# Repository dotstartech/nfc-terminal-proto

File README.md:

# nfc-terminal-proto
NFC Terminal Prototype

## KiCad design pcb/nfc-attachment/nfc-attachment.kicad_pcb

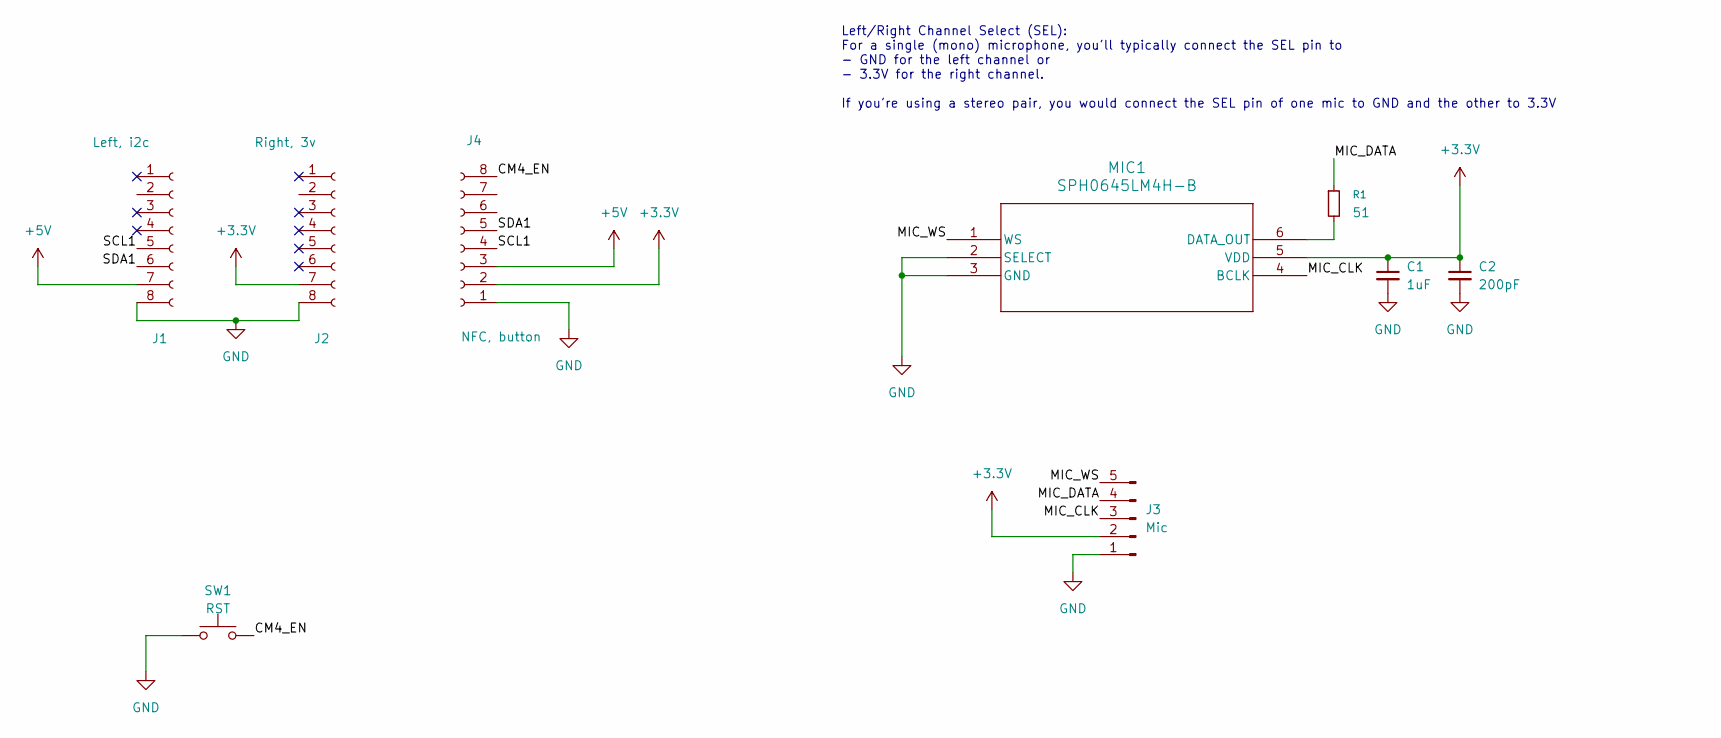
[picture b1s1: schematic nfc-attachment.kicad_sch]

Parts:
C1: 1uF; C_0603_1608Metric
C2: 200pF; C_0603_1608Metric
J1: Left, i2c; PinHeader_1x08_P2.54mm_Vertical
J2: Right, 3v; PinHeader_1x08_P2.54mm_Vertical
J3: Mic; PinHeader_1x05_P2.54mm_Vertical
J4: NFC, button; PinHeader_1x08_P2.54mm_Vertical
MIC1: SPH0645LM4H-B; SPH0645LM4H-B_KNO
R1: 51; R_0402_1005Metric
SW1: RST; SW_SPST_PTS810; LCSC C116501

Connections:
+3.3V: C1.1, C2.1, J2.7, J3.2, J4.2, MIC1.5 (VDD)
+5V: J1.7, J4.3
/CM4_EN: J4.8, SW1.2
/MIC_CLK: J3.3, MIC1.4 (BCLK)
/MIC_DATA: J3.4, R1.1
/MIC_WS: J3.5, MIC1.1 (WS)
/SCL1: J1.5, J4.4
/SDA1: J1.6, J4.5
GND: C1.2, C2.2, J1.8, J2.8, J3.1, J4.1, MIC1.2 (SELECT), MIC1.3 (GND), SW1.1
unnamed: MIC1.6 (DATA_OUT), R1.2

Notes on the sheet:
Left/Right Channel Select (SEL): For a single (mono) microphone, you'll typically connect the SEL pin to - GND for the left channel or - 3.3V for the right channel. If you're using a stereo pair, you would connect the SEL pin of one mic to GND and the other to 3.3V

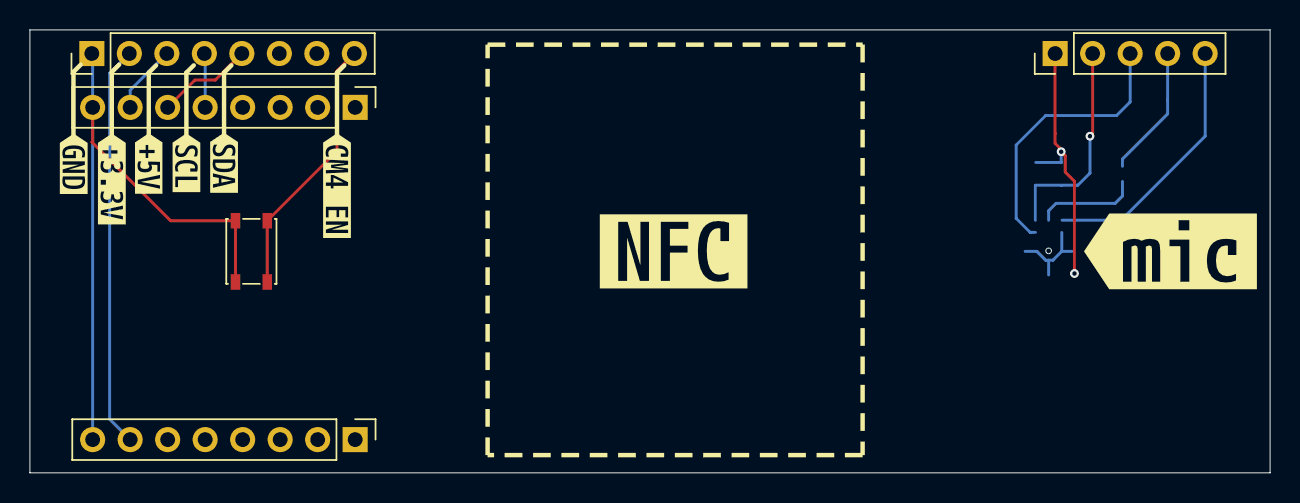
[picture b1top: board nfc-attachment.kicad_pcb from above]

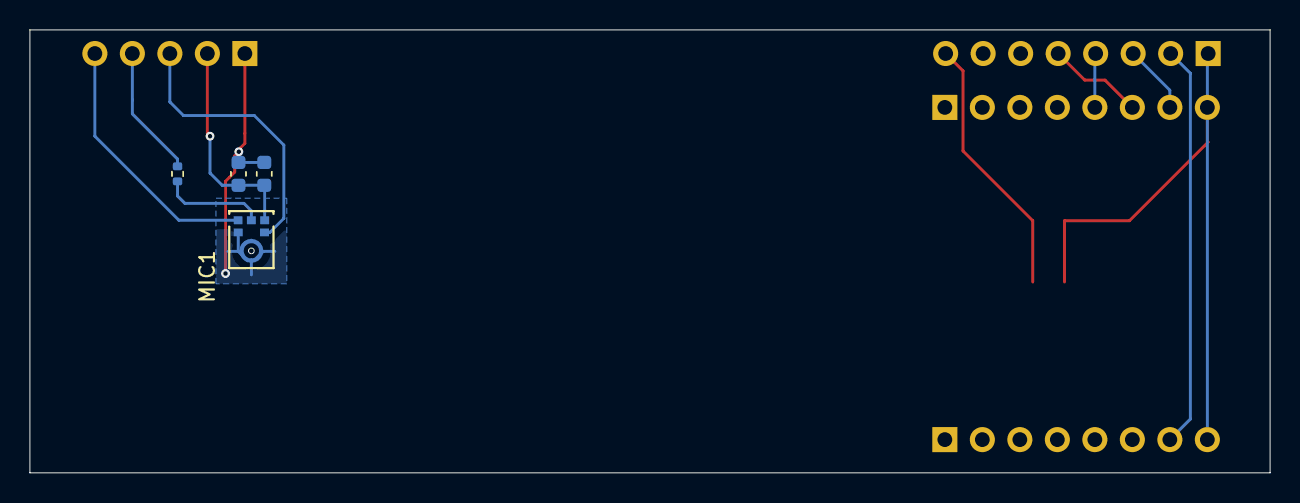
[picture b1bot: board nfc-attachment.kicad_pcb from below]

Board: 2 copper layers, 84.0 x 30.0 mm, 17 parts (4 on the bottom side), 10 nets.

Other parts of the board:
kibuzzard-68ADC165: G***; kibuzzard-68ADC165
kibuzzard-68ADC191: G***; kibuzzard-68ADC191
kibuzzard-68AEE2C2: G***; kibuzzard-68AEE2C2
kibuzzard-68AEE2D0: G***; kibuzzard-68AEE2D0
kibuzzard-68AEE2DF: G***; kibuzzard-68AEE2DF
kibuzzard-68AEE21F: G***; kibuzzard-68AEE21F
kibuzzard-68AEE211: G***; kibuzzard-68AEE211
kibuzzard-68AEE235: G***; kibuzzard-68AEE235

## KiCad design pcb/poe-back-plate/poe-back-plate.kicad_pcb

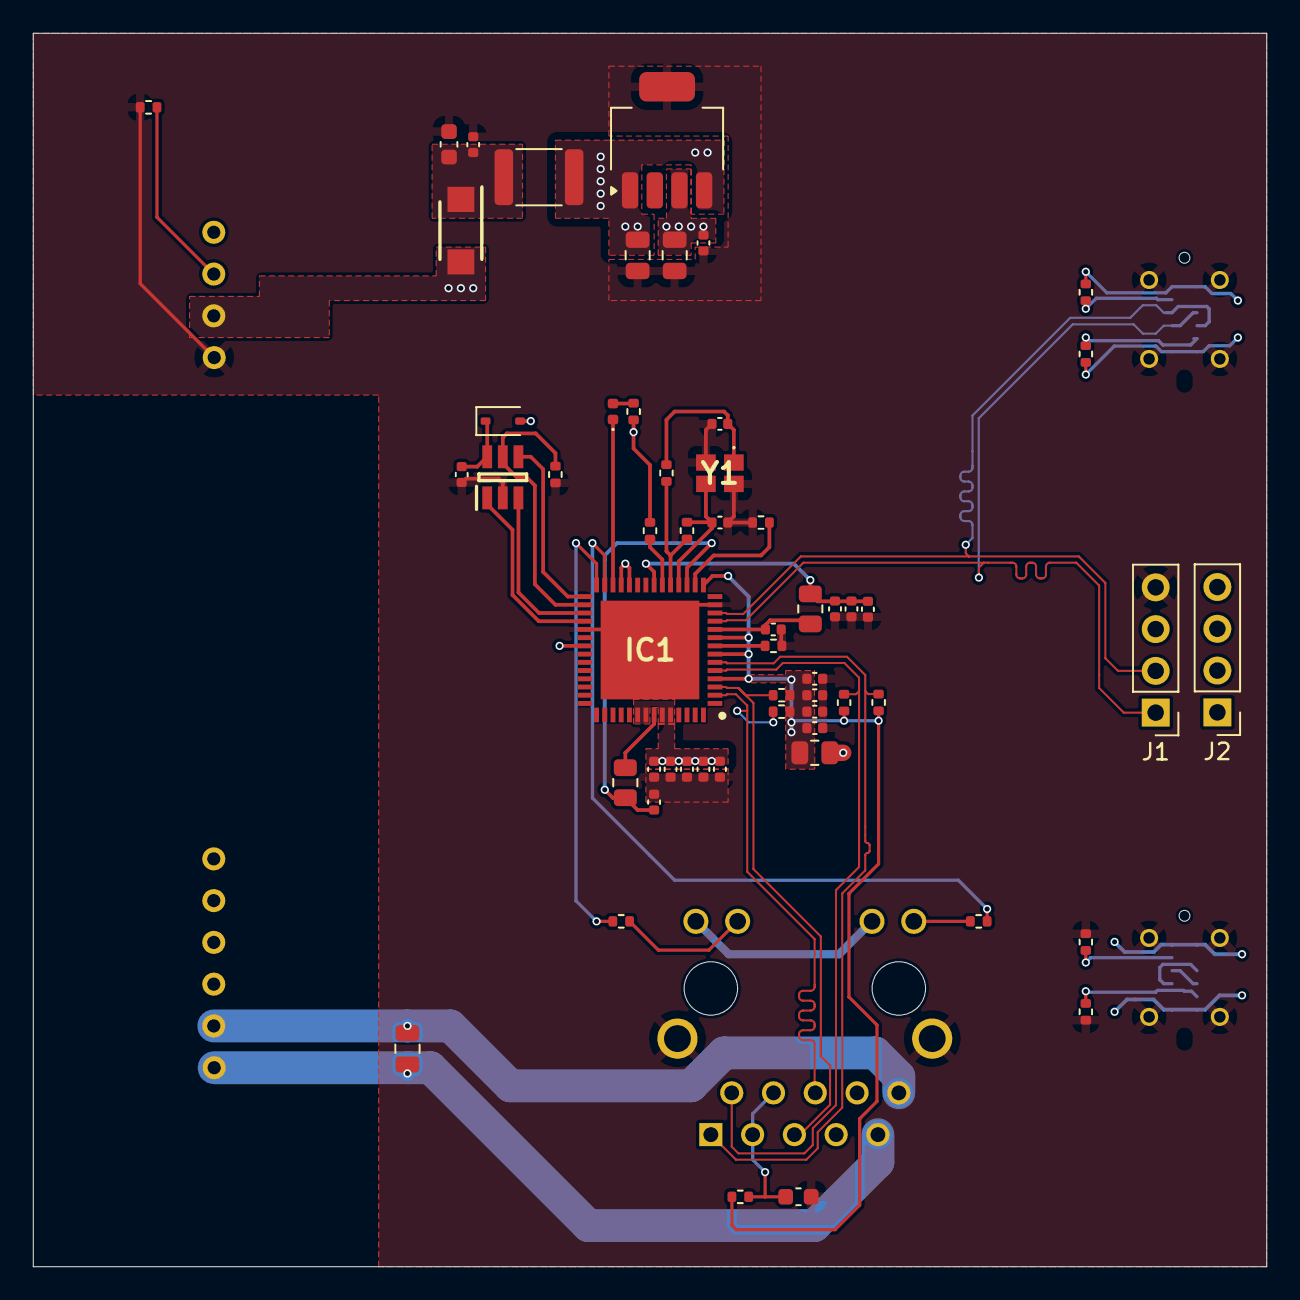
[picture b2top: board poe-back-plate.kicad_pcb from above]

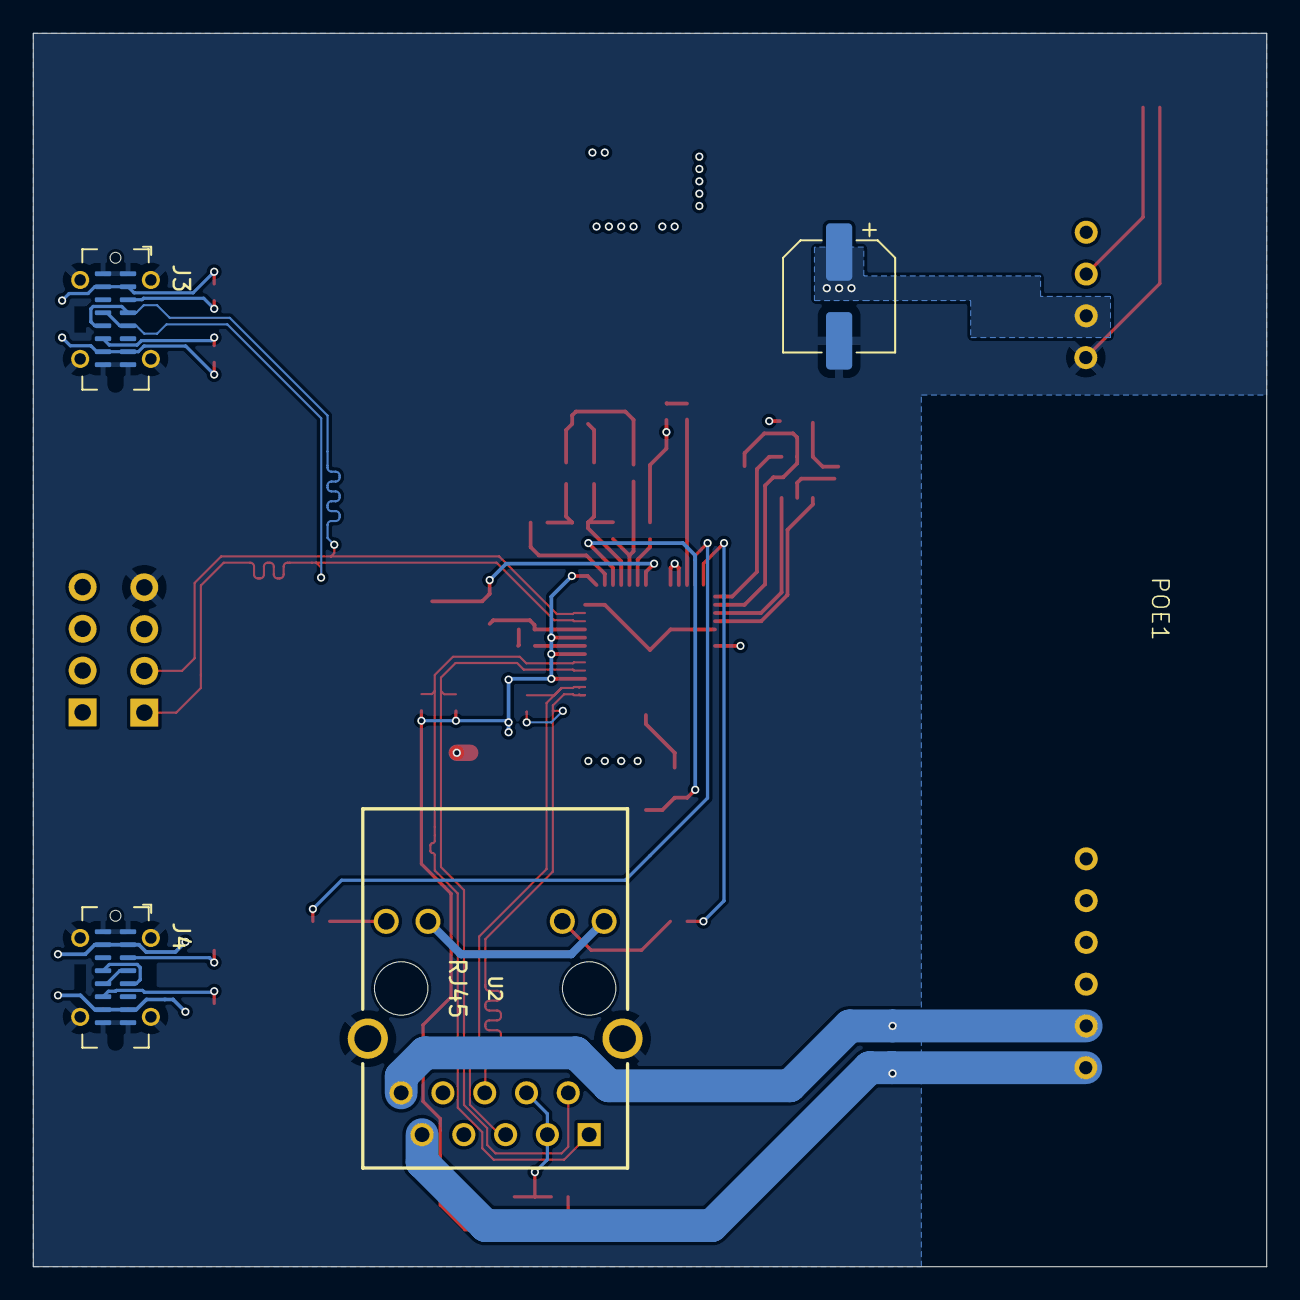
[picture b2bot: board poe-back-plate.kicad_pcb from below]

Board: 6 copper layers, 75.0 x 75.0 mm, 61 parts (5 on the bottom side), 42 nets.

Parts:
C1, C2, C3, C4, C5, C6, C7, C8, C9, C11, C12, C13, C14, C16, C20, C22: 100nF; C_0402_1005Metric
C10: 1uF; C_0402_1005Metric
C15, C18: 24pF; C_0402_1005Metric
C17, C19: 1uF; C_0805_2012Metric
C21: 1uF; C_0603_1608Metric
C23: 22nF; C_0603_1608Metric
C24: 10nF; C_0805_2012Metric
C25: 470µF; CP_Elec_6.3x7.7
D1: GREEN; LED_0402_1005Metric
D2: B0540WS; D_SOD-323
D3: SS54F; SODFL4626X120N
FB1, FB2, FB3: BLM21PG221SN1D; R_0805_2012Metric
FB4: CBM453215U101T; R_1812_4532Metric
IC1: LAN9500A-ABZJ; QFN50P800X800X100-57N-D
IC2: 93LC66AT-I_OT; SOT95P270X145-6N
J1: USB + Power; PinHeader_1x04_P2.54mm_Vertical
J2: UART + I2C; PinHeader_1x04_P2.54mm_Vertical
J3, J4: USB_C_Receptacle_USB2.0_14P; USB_C_Receptacle_G-Switch_GT-USB-7051x
POE1: AG5405
R1, R2: 12K; R_0402_1005Metric
R3, R5: 0; R_0402_1005Metric
R4: 1M; R_0402_1005Metric
R6, R12, R13: 3.3K; R_0402_1005Metric
R7: 10K; R_0402_1005Metric
R8, R10: 56K; R_0402_1005Metric
R9, R11: 5.1K; R_0402_1005Metric
R14: 10; R_0402_1005Metric
R15, R16, R17, R18: 49.9; R_0402_1005Metric
R19: 50K; R_0402_1005Metric
U1: LP38693MP-3.3; SOT-223-5
U2: HY931147C
Y1: ECS-250-18-36B2-CTY-TR; ECS2501836B2CTYTR

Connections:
+3.3V: C1.2, C2.2, C4.2, C6.2, C8.2, C19.2, C20.2, D2.2 (A), FB1.1, IC1.24 (NRESET), IC1.25 (VDD33IO_1), IC1.35 (VDD33IO_2), IC1.48 (VDD33IO_3), IC1.49 (TEST1), IC1.51 (VDD33IO_4), IC1.52 (VDD33IO_5), R3.1, R6.2, U1.3 (OUT), U2.P$11 (Y+), U2.P$13 (G+)
+5V: C17.2, FB4.2, J1.3, J3.A4 (VBUS), J3.A9 (VBUS), J3.B4 (VBUS), J3.B9 (VBUS), J4.A4 (VBUS), J4.A9 (VBUS), J4.B4 (VBUS), J4.B9 (VBUS), R8.2, R10.2, U1.1 (EN), U1.4 (IN)
/PoE/ETH1_LEDG: IC1.27 (NLNKA_LED/GPIO9), R12.2
/PoE/ETH1_LEDY: IC1.28 (NSPD_LED/GPIO10), R13.2
/PoE/POE_5V: C21.1, C22.1, D3.1 (K), FB4.1
/PoE/RXN: IC1.5 (RXN), R15.2, U2.P$2 (RX-)
/PoE/RXP: IC1.6 (RXP), R16.2, U2.P$1 (RX+)
/PoE/TXN: IC1.2 (TXN), R17.2, U2.P$6 (TX-)
/PoE/TXP: IC1.3 (TXP), R18.2, U2.P$5 (TX+)
/PoE/VDD33A: C3.2, C5.2, C7.2, C9.2, FB1.2, IC1.4 (VDD33A_1), IC1.7 (NC_1), IC1.9 (VDD33A_2), IC1.15 (VDD33A_3), R14.1, R15.1, R16.1, R17.1, R18.1
/USB to Ethernet/CRYSTAL_XI: C18.2, IC1.18 (XI), R4.2, Y1.3 (OUT/IN)
/USB to Ethernet/CRYSTAL_XO: IC1.19 (XO), R4.1, R5.1
/USB to Ethernet/EECLK_GPIO3: IC1.29 (EECLK/PWR_SEL), IC2.4 (CLK)
/USB to Ethernet/EECS_GPIO0: IC1.30 (EECS), IC2.5 (CS), R7.1
/USB to Ethernet/EEDI_GPIO1: IC1.32 (EEDI), IC2.1 (DO)
/USB to Ethernet/EEDO_GPIO2: IC1.31 (EEDO/AUTOMDIX_EN), IC2.3 (DI)
/USB to Ethernet/ETH1_LED_FDX: D1.1 (K), IC1.26 (NFDX_LED/GPIO8)
/USB to Ethernet/USBDN: IC1.11 (USBDM), J1.1, J3.A7 (D-), J3.B7 (D-)
/USB to Ethernet/USBDP: IC1.12 (USBDP), J1.2, J3.A6 (D+), J3.B6 (D+)
/USB to Ethernet/VDDCORE: C10.2, C11.2, C12.2, FB2.1, FB3.1, IC1.21 (VDDCORE_1), IC1.50 (VDDCORE_2)
/USB to Ethernet/VDDPLL: C14.2, FB3.2, IC1.10 (VDDPLL)
/USB to Ethernet/VDDUSBPLL: C13.2, FB2.2, IC1.17 (VDDUSBPLL)
GND: C1.1, C2.1, C3.1, C4.1, C5.1, C6.1, C7.1, C8.1, C9.1, C10.1, C11.1, C12.1, C13.1, C14.1, C15.1, C16.1, C17.1, C18.1, C19.1, C20.1, C21.2, C22.2, C23.2, C25.2, IC1.13 (TEST2), IC1.33 (TEST3), IC1.57 (VSS), IC2.2 (VSS), J1.4, J3.A1 (GND), J3.A12 (GND), J3.B1 (GND), J3.B12 (GND), J3.S1 (SHIELD), J4.A1 (GND), J4.A12 (GND), J4.B1 (GND), J4.B12 (GND), J4.S1 (SHIELD), POE1.7 (-VDC), R1.1, R2.1, R7.2, R9.2, R11.2, R19.2, U1.5 (GND), U2.GND1, U2.GND2, Y1.2 (GND_1), Y1.4 (GND_2)
unnamed: D1.2 (A), R6.1
unnamed: C16.2, D2.1 (K), IC2.6 (VCC)
unnamed: C25.1, D3.2 (A), POE1.8 (+VDC_)
unnamed: IC1.8 (EXRES), R1.2
unnamed: IC1.16 (USBRBIAS), R2.2
unnamed: IC1.20 (VBUS_DET), R3.2
unnamed: J3.A5 (CC1), R8.1
unnamed: J3.B5 (CC2), R10.1
unnamed: J4.A5 (CC1), R9.1
unnamed: J4.B5 (CC2), R11.1
unnamed: J4.A6 (D+), J4.B6 (D+)
unnamed: J4.A7 (D-), J4.B7 (D-)
unnamed: POE1.9 (ADJ), R19.1
unnamed: C24.1, POE1.1 (VIN+), U2.P$9 (V+)
unnamed: C24.2, POE1.2 (VIN-), U2.P$10 (V-)
unnamed: R12.1, U2.P$14 (G-)
unnamed: C23.1, R14.2, U2.P$3 (RXCT), U2.P$4 (TXCT)
unnamed: R13.1, U2.P$12 (Y-)
unnamed: C15.2, R5.2, Y1.1 (IN/OUT)

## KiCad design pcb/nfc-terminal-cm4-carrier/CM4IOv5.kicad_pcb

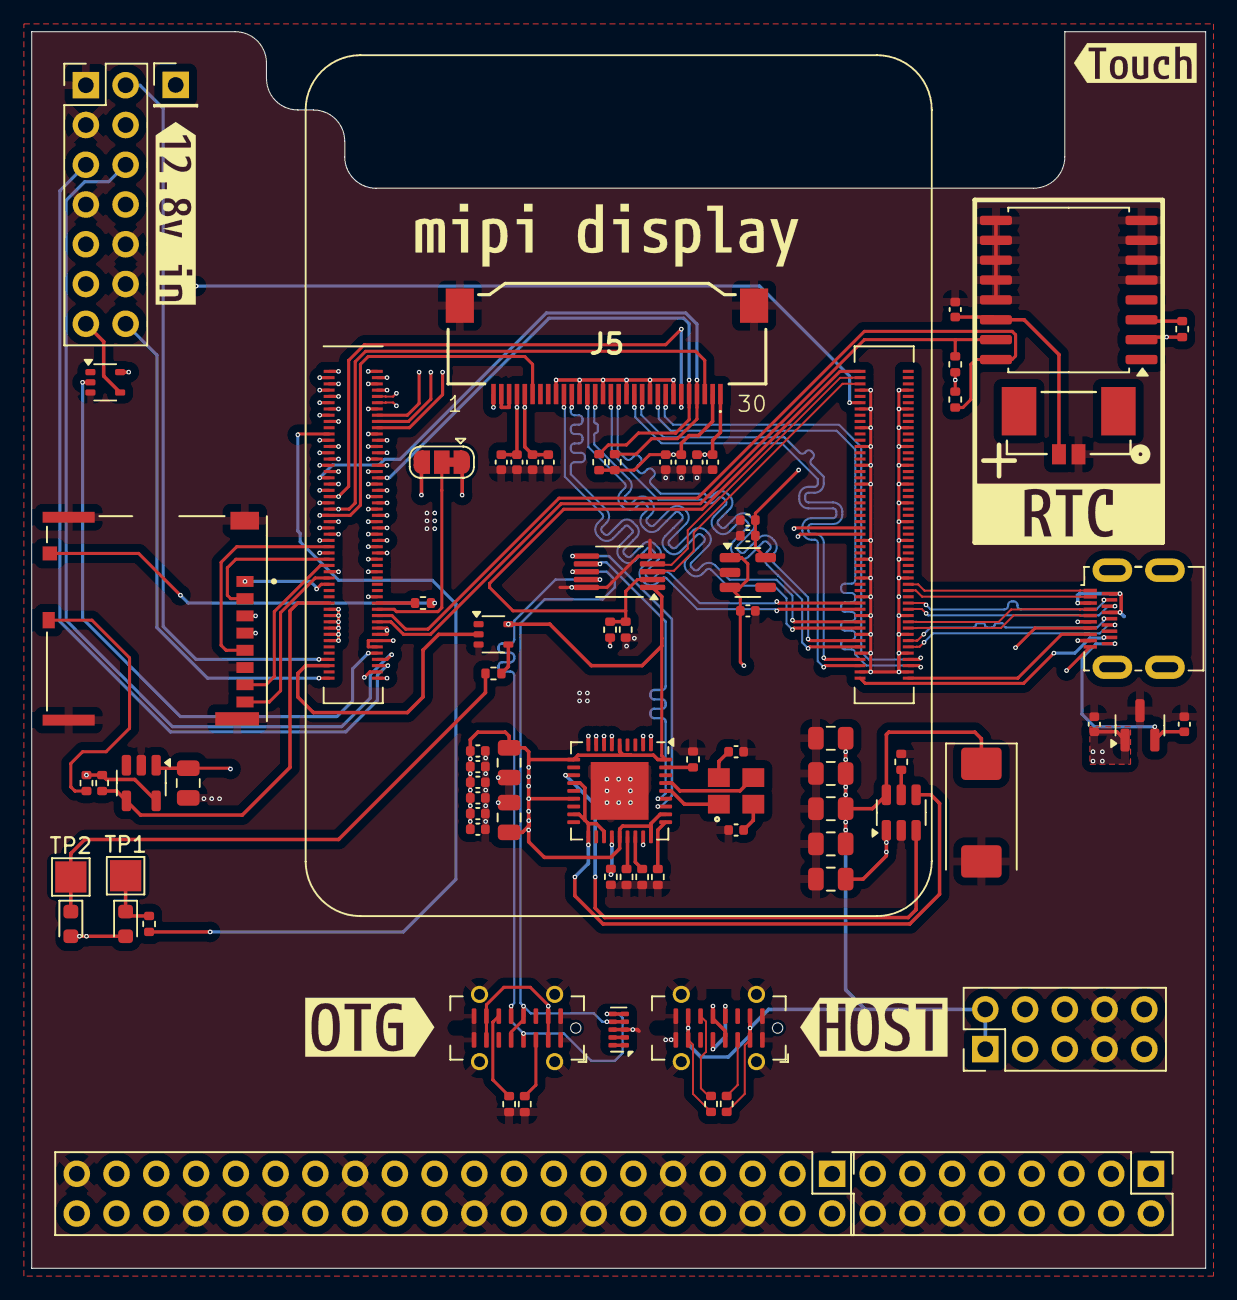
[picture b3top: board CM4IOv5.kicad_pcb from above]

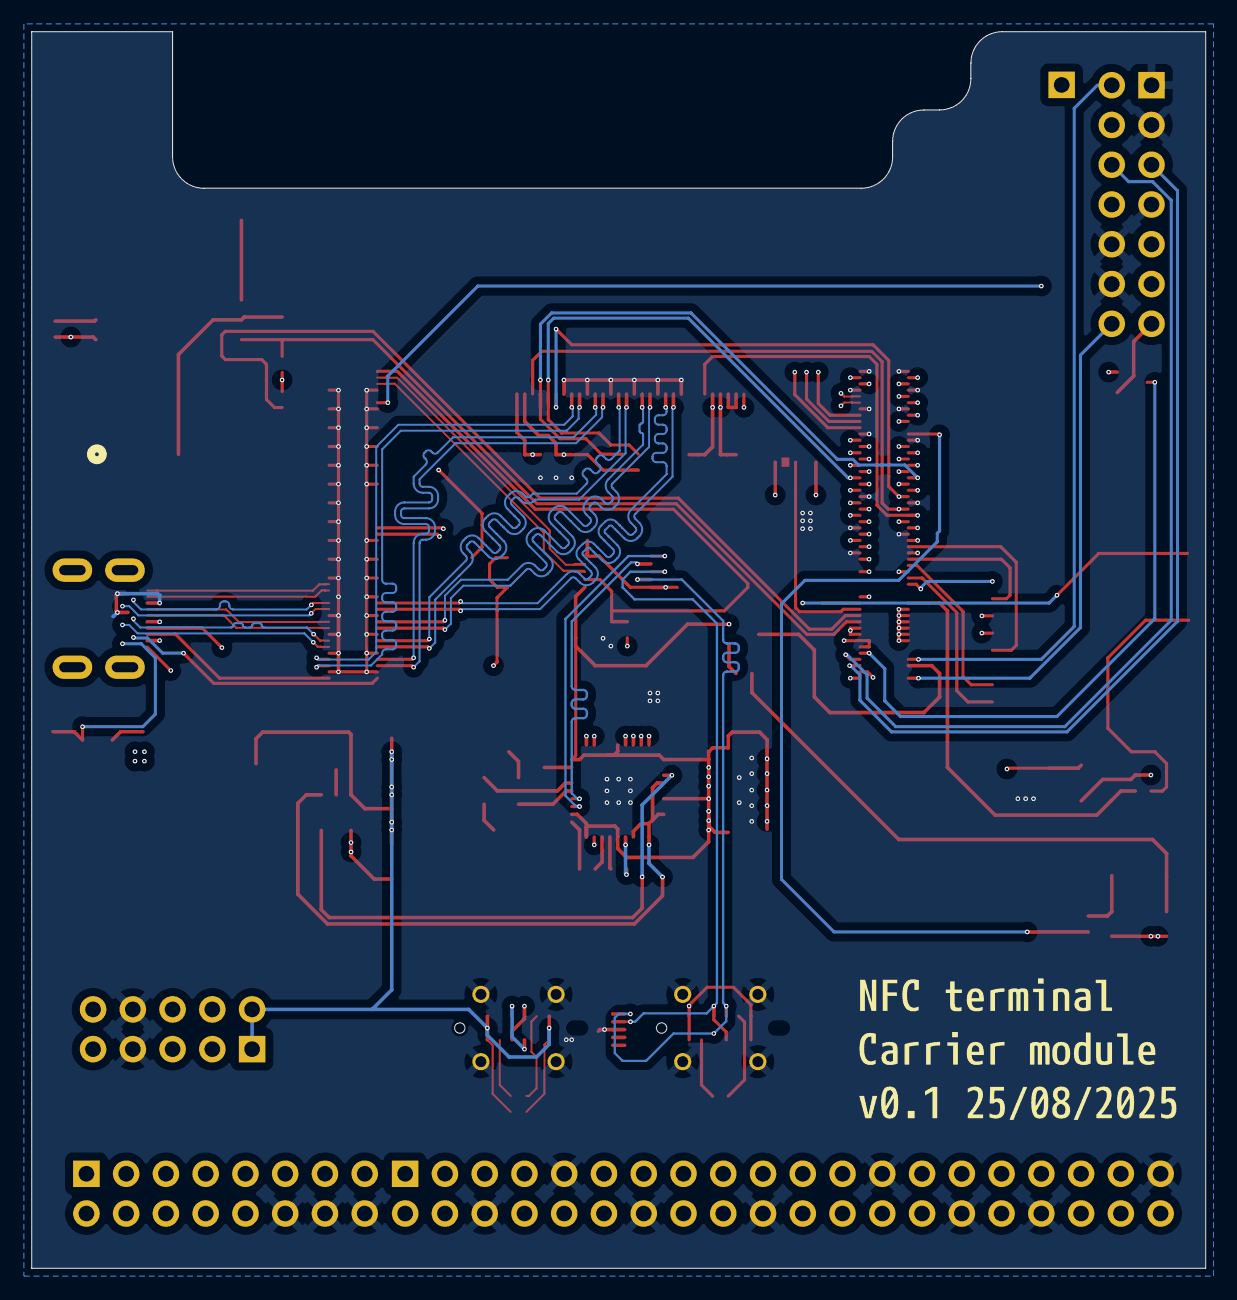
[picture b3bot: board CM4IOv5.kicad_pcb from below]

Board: 6 copper layers, 75.0 x 79.0 mm, 89 parts (2 on the bottom side), 132 nets.

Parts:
C1, C2: 27pF; C_0402_1005Metric
C3, C4, C11, C13, C14, C15, C16, C31: 10u; C_0805_2012Metric
C5, C6, C7, C8, C9, C10, C17, C18, C19, C22, C23, C24, C27, C28: 100n; C_0402_1005Metric
C12: 100uF; CP_EIA-7343-31_Kemet-D
C20, C21: 10uF; C_0402_1005Metric
C25, C26, C29, C30: 1uF; C_0402_1005Metric
D1: LED Green; LED_0603_1608Metric
D2: LED Red; LED_0603_1608Metric
J1, J2: USB_C_Receptacle_USB2.0_14P; USB_C_Receptacle_G-Switch_GT-USB-7051x
J3: Conn_02x05_Odd_Even; PinHeader_2x05_P2.54mm_Vertical
J4: Conn_01x02_Socket; CONN02_533984002_MOL
J5: F31L-1A7H1-11030; F31L1A7H111030
J6: 690-019-298-412; HDMI_Micro-D_Molex_46765-1x01
J7: Conn_02x07_Odd_Even; PinHeader_2x07_P2.54mm_Vertical
J10: THD-20-R; PinHeader_2x20_P2.54mm_Vertical
J15: THD-20-R; PinHeader_2x08_P2.54mm_Vertical
J16: Micro_SD_Card_Det; SDCARD_MOLEX_503398-1892
J17: UART; PinHeader_1x01_P2.54mm_Vertical
JP1: GPIO reference; SolderJumper-3_P1.3mm_Bridged12_RoundedPad1.0x1.5mm
Module1: ComputeModule4; Raspberry-Pi-4-Compute-Module
R1, R2, R14, R15: 2.2K 1%; R_0402_1005Metric
R3, R4, R5, R7: 36K 1%; R_0402_1005Metric
R6, R22: 12K 1%; R_0402_1005Metric
R8, R9: 5.1k; R_0402_1005Metric
R10, R12: 56K; R_0402_1005Metric
R11: 15K 1%; R_0402_1005Metric
R13: 10K; R_0402_1005Metric
R16, R19: 1k; R_0402_1005Metric
R20, R21: nf; R_0402_1005Metric
R23, R24: 4.7k; R_0402_1005Metric
TP1, TP2: TestPoint; TestPoint_Pad_2.0x2.0mm
U1: FSUSB42MUX; MSOP-10_3x3mm_P0.5mm
U2: USB2514B-I/M2; QFN-36-1EP_6x6mm_P0.5mm_EP3.7x3.7mm
U3: TPD4EUSB30; USON-10_2.5x1.0mm_P0.5mm
U4: AP22653W6; SOT-23-6
U5: DS3231M; SOIC-16W_7.5x10.3mm_P1.27mm
U6: RT9742SNGV; SOT-23
U7: LP5907MFX-2.8; SOT-23-5
U8, U9: 74LVC1G07SE-7; SOT-353_SC-70-5
U10: RT9742GGJ5; SOT-23-5
Y1: ABM8G-24.000MHZ-18-D2Y-T; ABM8G
kibuzzard-68AB3D2F: G***; kibuzzard-68AB3D2F
kibuzzard-68AB3EB0: G***; kibuzzard-68AB3EB0
kibuzzard-68AB3F8D: G***; kibuzzard-68AB3F8D
kibuzzard-68AB3F22: G***; kibuzzard-68AB3F22
kibuzzard-68AB3FA7: G***; kibuzzard-68AB3FA7
kibuzzard-68AB540C: G***; kibuzzard-68AB540C
kibuzzard-68AC31CB: G***; kibuzzard-68AC31CB
kibuzzard-68AC3314: G***; kibuzzard-68AC3314

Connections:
+2.8v: C21.2, C22.2, C24.1, C26.1, C28.1, C30.1, J5.4 (VCI_4), J5.5 (IOVCC_5), U7.5 (OUT)
/+3.3v: C3.1, C4.1, C5.1, C6.1, C7.1, C8.1, C9.1, C10.1, C20.2, C23.1, C25.1, C27.1, C29.1, D1.2 (A), D2.2 (A), J5.29 (TP_VCI_29), J5.30 (TP_IOVCC_30), J10.1, J10.17, J15.15, JP1.1 (A), Module1.84 (+3.3v_(Output)), Module1.86 (+3.3v_(Output)), R13.2, R14.1, R15.1, R20.1, R22.1, R23.1, R24.1, U1.1 (VCC), U2.5 (VDDA33), U2.10 (VDDA33), U2.15 (VDD33), U2.23 (VDD33), U2.27 (VBUS_DET), U2.29 (VDDA33), U2.36 (VDDA33), U5.2 (VCC), U7.1 (IN), U7.3 (EN), U9.5 (VCC), U10.5 (IN)
/+5v: C11.1, C18.1, J10.2, J10.4, J15.13, Module1.77 (+5v_(Input)), Module1.79 (+5v_(Input)), Module1.81 (+5v_(Input)), Module1.83 (+5v_(Input)), Module1.85 (+5v_(Input)), Module1.87 (+5v_(Input)), U4.1 (IN), U6.1 (IN), U8.5 (VCC)
/CM4_GPIO ( Ethernet, GPIO, SDCARD)/+1.8v: JP1.3 (B), Module1.88 (+1.8v_(Output)), Module1.90 (+1.8v_(Output))
/CM4_GPIO ( Ethernet, GPIO, SDCARD)/AIN0: J7.5, Module1.96 (AnalogIP0)
/CM4_GPIO ( Ethernet, GPIO, SDCARD)/AIN1: J7.6, Module1.94 (AnalogIP1)
/CM4_GPIO ( Ethernet, GPIO, SDCARD)/EEPROM_nWP: J7.4, Module1.20 (EEPROM_nWP)
/CM4_GPIO ( Ethernet, GPIO, SDCARD)/ETH_LEDG: J15.9, Module1.17 (Ethernet_nLED2(3.3v))
/CM4_GPIO ( Ethernet, GPIO, SDCARD)/ETH_LEDY: J15.10, Module1.15 (Ethernet_nLED3(3.3v))
/CM4_GPIO ( Ethernet, GPIO, SDCARD)/GLOBAL_EN: J7.14, Module1.99 (Global_EN)
/CM4_GPIO ( Ethernet, GPIO, SDCARD)/GPIO2: J10.3, Module1.58 (GPIO2)
/CM4_GPIO ( Ethernet, GPIO, SDCARD)/GPIO3: J10.5, Module1.56 (GPIO3)
/CM4_GPIO ( Ethernet, GPIO, SDCARD)/GPIO4: J10.7, Module1.54 (GPIO4)
/CM4_GPIO ( Ethernet, GPIO, SDCARD)/GPIO5: J10.29, Module1.34 (GPIO5)
/CM4_GPIO ( Ethernet, GPIO, SDCARD)/GPIO6: J10.31, Module1.30 (GPIO6)
/CM4_GPIO ( Ethernet, GPIO, SDCARD)/GPIO7: J10.26, Module1.37 (GPIO7)
/CM4_GPIO ( Ethernet, GPIO, SDCARD)/GPIO8: J10.24, Module1.39 (GPIO8)
/CM4_GPIO ( Ethernet, GPIO, SDCARD)/GPIO9: J10.21, Module1.40 (GPIO9)
/CM4_GPIO ( Ethernet, GPIO, SDCARD)/GPIO10: J10.19, Module1.44 (GPIO10)
/CM4_GPIO ( Ethernet, GPIO, SDCARD)/GPIO11: J10.23, Module1.38 (GPIO11)
/CM4_GPIO ( Ethernet, GPIO, SDCARD)/GPIO12: J10.32, Module1.31 (GPIO12)
/CM4_GPIO ( Ethernet, GPIO, SDCARD)/GPIO13: J10.33, Module1.28 (GPIO13)
/CM4_GPIO ( Ethernet, GPIO, SDCARD)/GPIO14: J10.8, Module1.55 (GPIO14)
/CM4_GPIO ( Ethernet, GPIO, SDCARD)/GPIO15: J10.10, Module1.51 (GPIO15)
/CM4_GPIO ( Ethernet, GPIO, SDCARD)/GPIO16: J10.36, Module1.29 (GPIO16)
/CM4_GPIO ( Ethernet, GPIO, SDCARD)/GPIO17: J10.11, Module1.50 (GPIO17)
/CM4_GPIO ( Ethernet, GPIO, SDCARD)/GPIO18: J10.12, Module1.49 (GPIO18)
/CM4_GPIO ( Ethernet, GPIO, SDCARD)/GPIO19: J10.35, Module1.26 (GPIO19)
/CM4_GPIO ( Ethernet, GPIO, SDCARD)/GPIO20: J10.38, Module1.27 (GPIO20)
/CM4_GPIO ( Ethernet, GPIO, SDCARD)/GPIO21: J10.40, Module1.25 (GPIO21)
/CM4_GPIO ( Ethernet, GPIO, SDCARD)/GPIO22: J10.15, Module1.46 (GPIO22)
/CM4_GPIO ( Ethernet, GPIO, SDCARD)/GPIO23: J5.6 (RESET_6), J10.16, Module1.47 (GPIO23)
/CM4_GPIO ( Ethernet, GPIO, SDCARD)/GPIO24: J5.28 (TP_RESET_28), J10.18, Module1.45 (GPIO24)
/CM4_GPIO ( Ethernet, GPIO, SDCARD)/GPIO25: J5.25 (TP_INT_25), J10.22, Module1.41 (GPIO25)
/CM4_GPIO ( Ethernet, GPIO, SDCARD)/GPIO26: J10.37, Module1.24 (GPIO26)
/CM4_GPIO ( Ethernet, GPIO, SDCARD)/GPIO27: J10.13, Module1.48 (GPIO27)
/CM4_GPIO ( Ethernet, GPIO, SDCARD)/GPIO_VREF: JP1.2 (C), Module1.78 (GPIO_VREF(1.8v/3.3v_Input))
/CM4_GPIO ( Ethernet, GPIO, SDCARD)/ID_SC: J5.27 (TP_SCL_27), J10.28, Module1.35 (ID_SC), R15.2
/CM4_GPIO ( Ethernet, GPIO, SDCARD)/ID_SD: J5.26 (TP_SDA_26), J10.27, Module1.36 (ID_SD), R14.2
/CM4_GPIO ( Ethernet, GPIO, SDCARD)/RUN_PG: Module1.92 (RUN_PG), U8.2
/CM4_GPIO ( Ethernet, GPIO, SDCARD)/Reserved: Module1.76 (Reserved), R21.1
/CM4_GPIO ( Ethernet, GPIO, SDCARD)/SCL0: Module1.80 (SCL0), R24.2, U5.16 (SCL)
/CM4_GPIO ( Ethernet, GPIO, SDCARD)/SDA0: Module1.82 (SDA0), R23.2, U5.15 (SDA)
/CM4_GPIO ( Ethernet, GPIO, SDCARD)/SD_CLK: J16.5 (CLK), Module1.57 (SD_CLK)
/CM4_GPIO ( Ethernet, GPIO, SDCARD)/SD_CMD: J16.3 (CMD), Module1.62 (SD_CMD)
/CM4_GPIO ( Ethernet, GPIO, SDCARD)/SD_DAT0: J16.7 (DAT0), Module1.63 (SD_DAT0)
/CM4_GPIO ( Ethernet, GPIO, SDCARD)/SD_DAT1: J16.8 (DAT1), Module1.67 (SD_DAT1)
/CM4_GPIO ( Ethernet, GPIO, SDCARD)/SD_DAT2: J16.1 (DAT2), Module1.69 (SD_DAT2)
/CM4_GPIO ( Ethernet, GPIO, SDCARD)/SD_DAT3: J16.2 (DAT3/CD), Module1.61 (SD_DAT3)
/CM4_GPIO ( Ethernet, GPIO, SDCARD)/SD_PWR: C31.1, J16.4 (VDD), U10.1 (OUT)
/CM4_GPIO ( Ethernet, GPIO, SDCARD)/SD_PWR_ON: Module1.75 (SD_PWR_ON), R22.2, U10.4 (EN)
/CM4_GPIO ( Ethernet, GPIO, SDCARD)/SYNC_IN: J7.8, Module1.16 (Ethernet_SYNC_IN(1.8v))
/CM4_GPIO ( Ethernet, GPIO, SDCARD)/SYNC_OUT: J7.9, Module1.18 (Ethernet_SYNC_OUT(1.8v))
/CM4_GPIO ( Ethernet, GPIO, SDCARD)/TRD0_N: J15.2, Module1.10 (Ethernet_Pair0_N)
/CM4_GPIO ( Ethernet, GPIO, SDCARD)/TRD0_P: J15.1, Module1.12 (Ethernet_Pair0_P)
/CM4_GPIO ( Ethernet, GPIO, SDCARD)/TRD1_N: J15.4, Module1.6 (Ethernet_Pair1_N)
/CM4_GPIO ( Ethernet, GPIO, SDCARD)/TRD1_P: J15.3, Module1.4 (Ethernet_Pair1_P)
/CM4_GPIO ( Ethernet, GPIO, SDCARD)/TRD2_N: J15.6, Module1.9 (Ethernet_Pair2_N)
/CM4_GPIO ( Ethernet, GPIO, SDCARD)/TRD2_P: J15.5, Module1.11 (Ethernet_Pair2_P)
/CM4_GPIO ( Ethernet, GPIO, SDCARD)/TRD3_N: J15.8, Module1.5 (Ethernet_Pair3_N)
/CM4_GPIO ( Ethernet, GPIO, SDCARD)/TRD3_P: J15.7, Module1.3 (Ethernet_Pair3_P)
/CM4_GPIO ( Ethernet, GPIO, SDCARD)/TV_OUT: J7.11, Module1.111 (VDAC_COMP)
/CM4_GPIO ( Ethernet, GPIO, SDCARD)/nPWR_LED: Module1.95 (nPI_LED_PWR), U9.2
/CM4_GPIO ( Ethernet, GPIO, SDCARD)/nRPIBOOT: J7.2, Module1.93 (nRPIBOOT)
/CM4_HighSpeed/+12.8v: J5.1 (LEDA_1), J17.1
/CM4_HighSpeed/DSI1_C_N: J5.17 (CLKN_17), Module1.187 (DSI1_C_N)
/CM4_HighSpeed/DSI1_C_P: J5.16 (CLKP_16), Module1.189 (DSI1_C_P)
/CM4_HighSpeed/DSI1_D0_N: J5.11 (MIPI_0N_11), Module1.175 (DSI1_D0_N)
/CM4_HighSpeed/DSI1_D0_P: J5.10 (MIPI_0P_10), Module1.177 (DSI1_D0_P)
/CM4_HighSpeed/DSI1_D1_N: J5.14 (MIPI_1N_14), Module1.181 (DSI1_D1_N)
/CM4_HighSpeed/DSI1_D1_P: J5.13 (MIPI_1P_13), Module1.183 (DSI1_D1_P)
/CM4_HighSpeed/DSI1_D2_N: J5.20 (MIPI_2N__20), Module1.193 (DSI1_D2_N)
/CM4_HighSpeed/DSI1_D2_P: J5.19 (MIPI_2P_19), Module1.195 (DSI1_D2_P)
/CM4_HighSpeed/DSI1_D3_N: J5.23 (MIPI_3N_23), Module1.194 (DSI1_D3_N)
/CM4_HighSpeed/DSI1_D3_P: J5.22 (MIPI_3P_22), Module1.196 (DSI1_D3_P)
/CM4_HighSpeed/HDMI0_CEC: J6.13 (CEC), Module1.151 (HDMI0_CEC)
/CM4_HighSpeed/HDMI0_CK_N: J6.12 (CK-), Module1.190 (HDMI0_CLK_N)
/CM4_HighSpeed/HDMI0_CK_P: J6.10 (CK+), Module1.188 (HDMI0_CLK_P)
/CM4_HighSpeed/HDMI0_D0_N: J6.9 (D0-), Module1.184 (HDMI0_TX0_N)
/CM4_HighSpeed/HDMI0_D0_P: J6.7 (D0+), Module1.182 (HDMI0_TX0_P)
/CM4_HighSpeed/HDMI0_D1_N: J6.6 (D1-), Module1.178 (HDMI0_TX1_N)
/CM4_HighSpeed/HDMI0_D1_P: J6.4 (D1+), Module1.176 (HDMI0_TX1_P)
/CM4_HighSpeed/HDMI0_D2_N: J6.3 (D2-), Module1.172 (HDMI0_TX2_N)
/CM4_HighSpeed/HDMI0_D2_P: J6.1 (D2+), Module1.170 (HDMI0_TX2_P)
/CM4_HighSpeed/HDMI0_HOTPLUG: J6.19 (HPD/HEAC-), Module1.153 (HDMI0_HOTPLUG)
/CM4_HighSpeed/HDMI0_SCL: J6.15 (SCL), Module1.200 (HDMI0_SCL)
/CM4_HighSpeed/HDMI0_SDA: J6.16 (SDA), Module1.199 (HDMI0_SDA)
/CM4_HighSpeed/HDMI_5v: C19.1, J6.18 (+5V), U6.2 (OUT)
/CM4_HighSpeed/USB2_N: Module1.103 (USB2_N), U1.4 (D_N)
/CM4_HighSpeed/USB2_P: Module1.105 (USB2_P), U1.3 (D_P)
/CM4_HighSpeed/USBOTG_ID: Module1.101 (USB_OTG_ID), R1.1, R2.2, U1.2 (SEL)
/RTC , Wakeup, FAN/nRTC_INT: R13.1, U5.3 (~INT/SQW)
/USB2-HUB/HD1_N: J2.A7 (D-), J2.B7 (D-), U2.1 (USBDM_DN1/PRT_DIS_M1)
/USB2-HUB/HD1_P: J2.A6 (D+), J2.B6 (D+), U2.2 (USBDP_DN1/PRT_DIS_P1)
/USB2-HUB/HD3_N: J3.3, U2.6 (USBDM_DN3/PRT_DIS_M3)
/USB2-HUB/HD3_P: J3.5, U2.7 (USBDP_DN3/PRT_DIS_P3)
/USB2-HUB/HD4_N: J3.4, U2.8 (USBDM_DN4/PRT_DIS_M4)
/USB2-HUB/HD4_P: J3.6, U2.9 (USBDP_DN4/PRT_DIS_P4)
/USB2-HUB/PWR1: U2.12 (PRTPWR1/BC_EN1), U4.3 (EN)
/USB2-HUB/USBD_N: J1.A7 (D-), J1.B7 (D-), U1.8 (HSD1_M), U3.4 (D2+), U3.7
/USB2-HUB/USBD_P: J1.A6 (D+), J1.B6 (D+), U1.9 (HSD1_P), U3.5 (D2-), U3.6
/USB2-HUB/USBH_N: U1.6 (HSD0_M), U2.30 (USBDM_UP)
/USB2-HUB/USBH_P: U1.7 (HSD0_P), U2.31 (USBDP_UP)
/USB2-HUB/VBUS: C12.1, C13.1, C14.1, C15.1, C16.1, J2.A4 (VBUS), J2.A9 (VBUS), J2.B4 (VBUS), J2.B9 (VBUS), J3.1, J3.2, R10.2, R12.2, U4.6 (OUT)
/USB2-HUB/nOCS1: U2.13 (OCS_N1), U2.17 (OCS_N2), U2.19 (OCS_N3), U2.21 (OCS_N4), U4.4 (nFault)
/nEXTRST: Module1.100 (nEXTRST), U2.26 (RESET_N)
GND: C1.2, C2.2, C3.2, C4.2, C5.2, C6.2, C7.2, C8.2, C9.2, C10.2, C11.2, C12.2, C13.2, C14.2, C15.2, C16.2, C17.2, C18.2, C19.2, C20.1, C21.1, C22.1, C23.2, C24.2, C25.2, C26.2, C27.2, C28.2, C29.2, C30.2, C31.2, J1.A1 (GND), J1.A12 (GND), J1.B1 (GND), J1.B12 (GND), J1.S1 (SHIELD), J2.A1 (GND), J2.A12 (GND), J2.B1 (GND), J2.B12 (GND), J2.S1 (SHIELD), J3.7, J3.8, J4.1, J5.2 (LEDK1_2), J5.3 (LEDK2_3), J5.9 (GND_9), J5.12 (GND_12), J5.15 (GND_15), J5.18 (GND_18), J5.21 (GND_21), J5.24 (GND_24), J5.31 (MP_1), J5.32 (MP_2), J6.2 (D2S), J6.5 (D1S), J6.8 (D0S), J6.11 (CKS), J6.17 (GND), J7.1, J7.3, J7.7, J7.10, J7.12, J10.6, J10.9, J10.14, J10.20, J10.25, J10.30, J10.34, J10.39, J15.12, J15.14, J15.16, J16.6 (VSS), J16.11 (SHIELD), Module1.1 (GND), Module1.2 (GND), Module1.7 (GND), Module1.8 (GND), Module1.13 (GND), Module1.14 (GND), Module1.22 (GND), Module1.23 (GND), Module1.32 (GND), Module1.33 (GND), Module1.42 (GND), Module1.43 (GND), Module1.52 (GND), Module1.53 (GND), Module1.59 (GND), Module1.60 (GND), Module1.65 (GND), Module1.66 (GND), Module1.71 (GND), Module1.74 (GND), Module1.98 (GND), Module1.107 (GND), Module1.108 (GND), Module1.113 (GND), Module1.114 (GND), Module1.119 (GND), Module1.120 (GND), Module1.125 (GND), Module1.126 (GND), Module1.131 (GND), Module1.132 (GND), Module1.137 (GND), Module1.138 (GND), Module1.144 (GND), Module1.150 (GND), Module1.155 (GND), Module1.156 (GND), Module1.161 (GND), Module1.162 (GND), Module1.167 (GND), Module1.168 (GND), Module1.173 (GND), Module1.174 (GND), Module1.179 (GND), Module1.180 (GND), Module1.185 (GND), Module1.186 (GND), Module1.191 (GND), Module1.192 (GND), Module1.197 (GND), Module1.198 (GND), R1.2, R3.2, R4.2, R5.2, R6.1, R7.2, R8.1, R9.1, R11.2, U1.5 (GND), U1.10 (nOE), U2.37 (VSS), U3.3 (GND), U3.8 (GND), U4.2 (GND), U5.5 (GND), U5.6 (GND), U5.7 (GND), U5.8 (GND), U5.9 (GND), U5.10 (GND), U5.11 (GND), U5.12 (GND), U5.13 (GND), U6.3 (GND), U7.2 (GND), U8.3 (GND), U9.3 (GND), U10.2 (GND)
unnamed: D1.1 (K), R16.1, TP1.1
unnamed: D2.1 (K), R19.1, TP2.1
unnamed: J1.A5 (CC1), R9.2
unnamed: J1.B5 (CC2), R8.2
unnamed: J1.A4 (VBUS), J1.A9 (VBUS), J1.B4 (VBUS), J1.B9 (VBUS), R2.1
unnamed: J2.A5 (CC1), R10.1
unnamed: J2.B5 (CC2), R12.1
unnamed: C17.1, J4.2, U5.14 (VBAT)
unnamed: J7.13, U8.4
unnamed: J16.10 (DET_A), R20.2
unnamed: J16.9 (DET_B), R21.2
unnamed: Module1.21 (PI_nLED_Activity), R16.2
unnamed: R19.2, U9.4
unnamed: R7.1, U2.25 (HS_IND/CFG_SEL1)
unnamed: R6.2, U2.35 (RBIAS)
unnamed: R3.1, U2.24 (SCL/SMBCLK/CFG_SEL0)
unnamed: R4.1, U2.22 (SDA/SMBDATA/NON_REM1)
unnamed: R5.1, U2.28 (SUSP_IND/LOCAL_PWR/NON_REM0)
unnamed: U2.33 (XTALIN/CLKIN), Y1.3 (XTAL_2)
unnamed: U2.32 (XTALOUT), Y1.1 (XTAL_1)
unnamed: U3.1 (D1+), U3.10
unnamed: U3.2 (D1-), U3.9
unnamed: R11.1, U4.5 (ILIM)
unnamed: C2.1, Y1.2 (GND_1)
unnamed: C1.1, Y1.4 (GND_2)

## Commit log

2025-08-12 Added roadmap document
2025-09-16 PCB carrier v0.1, poe wip
2025-09-21 Adde PN7160 Linux integration docs
